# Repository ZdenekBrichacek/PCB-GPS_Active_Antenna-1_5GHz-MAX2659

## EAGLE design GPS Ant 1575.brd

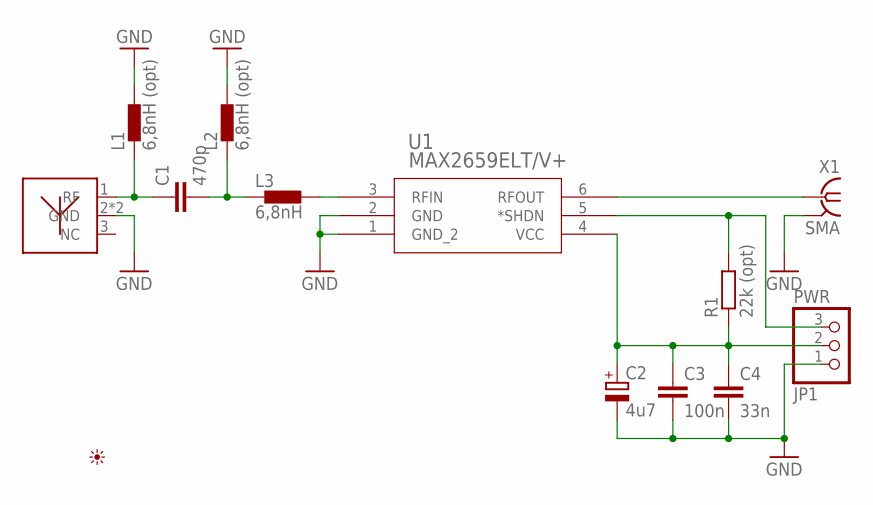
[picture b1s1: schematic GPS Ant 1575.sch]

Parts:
ANT1: 1575AT54A0010
C1: 470p; C0603
C2: 4u7; SMC_A
C3: 100n; C0603
C4: 33n; C0603
JP1: PWR; 1X03
L1, L2: 6,8nH (opt); 0402
L3: 6,8nH; 0402
PICTO1: PICTO_1
R1: 22k (opt); R0603
U1: MAX2659ELT/V+; 21-0147E
X1: SMA; J502-ND-142-0701-801/806

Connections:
GND: ANT1.2 (GND), ANT1.4 (GND), C2.-, C3.2, C4.2, JP1.1, L1.2, L2.2, U1.1 (GND_2), U1.2 (GND), X1.G@1 (2), X1.G@2 (2), X1.G@3 (2), X1.G@4 (2)
unnamed: ANT1.1 (RF), C1.1, L1.1
unnamed: C1.2, L2.1, L3.1
unnamed: L3.2, U1.3 (RFIN)
unnamed: U1.6 (RFOUT), X1.1
SHDN: JP1.3, R1.2, U1.5 (*SHDN)
VCC: C2.+, C3.1, C4.1, JP1.2, R1.1, U1.4 (VCC)

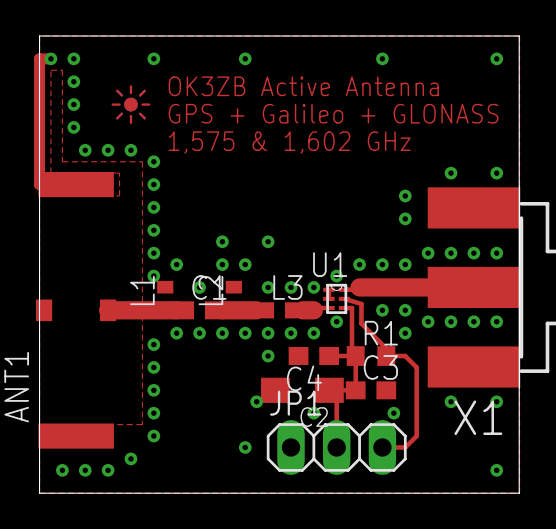
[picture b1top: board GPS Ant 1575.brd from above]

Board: 2 copper layers, 26.6 x 25.4 mm, 13 parts (0 on the bottom side), 7 nets.

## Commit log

2017-10-10 :confetti_ball: Added .gitattributes & .gitignore files
2017-10-10 Initial version
